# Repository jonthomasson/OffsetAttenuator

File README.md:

# OffsetAttenuator
4MHz Offset Attenuator used in Ham Radio Fox Hunting.

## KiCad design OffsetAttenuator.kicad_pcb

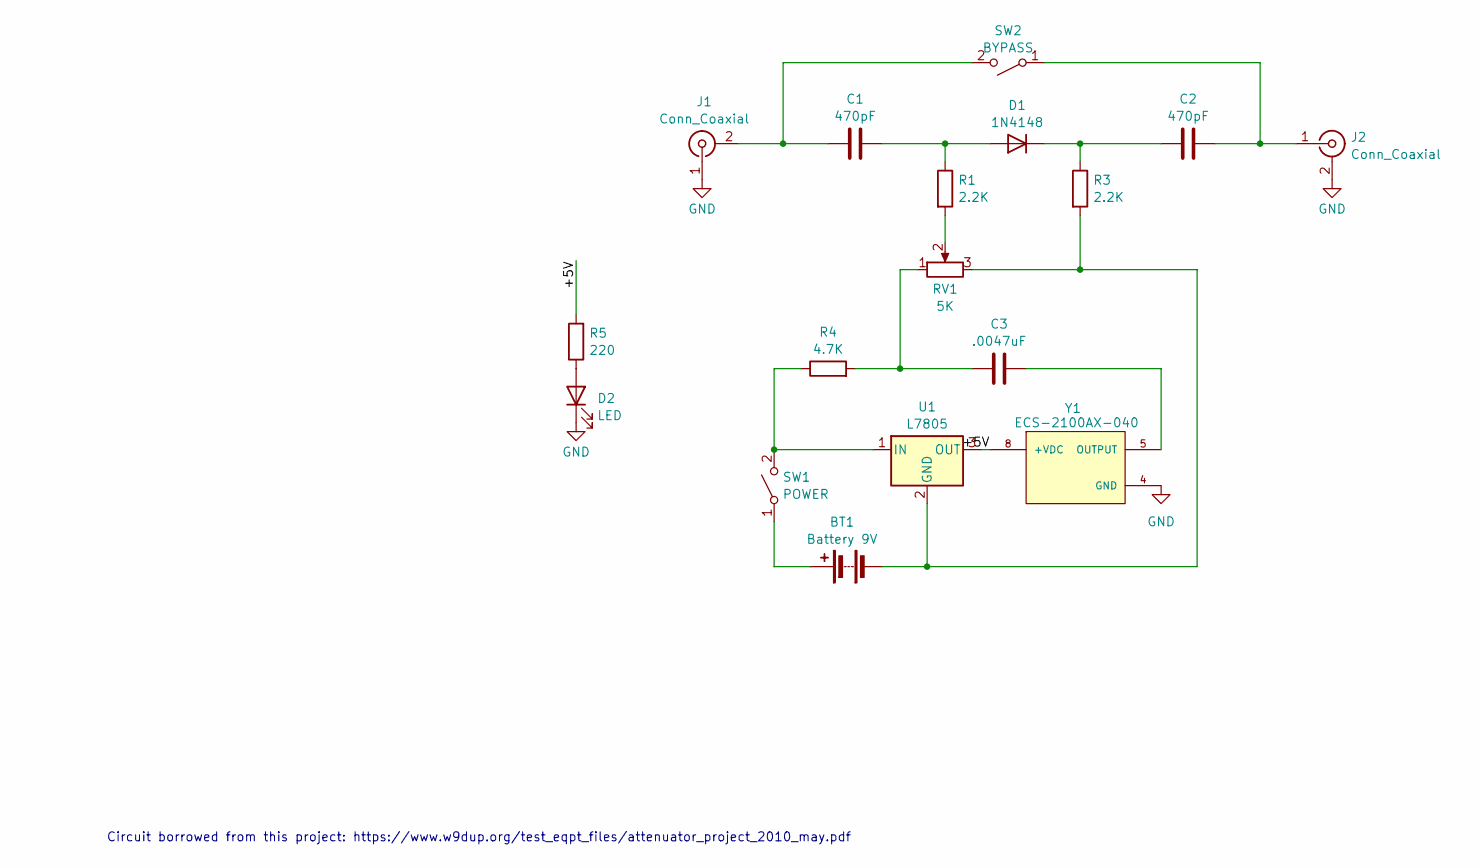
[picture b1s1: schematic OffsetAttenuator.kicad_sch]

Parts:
BT1: Battery 9V; PinHeader_1x02_P2.54mm_Vertical
C1, C2: 470pF; C_Disc_D5.0mm_W2.5mm_P5.00mm
C3: .0047uF; C_Disc_D5.0mm_W2.5mm_P5.00mm
D1: 1N4148; D_DO-35_SOD27_P7.62mm_Horizontal
D2: LED; LED_D5.0mm
J1, J2: Conn_Coaxial; CONBNC002
R1, R3: 2.2K; R_Axial_DIN0309_L9.0mm_D3.2mm_P12.70mm_Horizontal
R4: 4.7K; R_Axial_DIN0309_L9.0mm_D3.2mm_P12.70mm_Horizontal
R5: 220; R_Axial_DIN0309_L9.0mm_D3.2mm_P12.70mm_Horizontal
RV1: 5K; TRIM_3310Y-001-502L
SW1: POWER; SWT3
SW2: BYPASS; SWT3
U1: L7805; TO-220-3_Vertical
Y1: ECS-2100AX-040; OSC_ECS-2100AX-040; PARTREV N/A

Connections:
/+5V: R5.2, U1.3 (OUT), Y1.8 (+VDC)
GND: D2.1 (K), J1.1 (In), J2.2 (Ext), Y1.4 (GND)
unnamed: BT1.1 (+), SW1.1 (A)
unnamed: BT1.2 (-), R3.2, RV1.3, U1.2 (GND)
unnamed: C3.1, R4.2, RV1.1
unnamed: C1.2, D1.2 (A), R1.1
unnamed: C2.1, D1.1 (K), R3.1
unnamed: D2.2 (A), R5.1
unnamed: C1.1, J1.2 (Ext), SW2.2 (B)
unnamed: C2.2, J2.1 (In), SW2.1 (A)
unnamed: R1.2, RV1.2
unnamed: R4.1, SW1.2 (B), U1.1 (IN)
unnamed: C3.2, Y1.5 (OUTPUT)

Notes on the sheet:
Circuit borrowed from this project: https://www.w9dup.org/test_eqpt_files/attenuator_project_2010_may.pdf

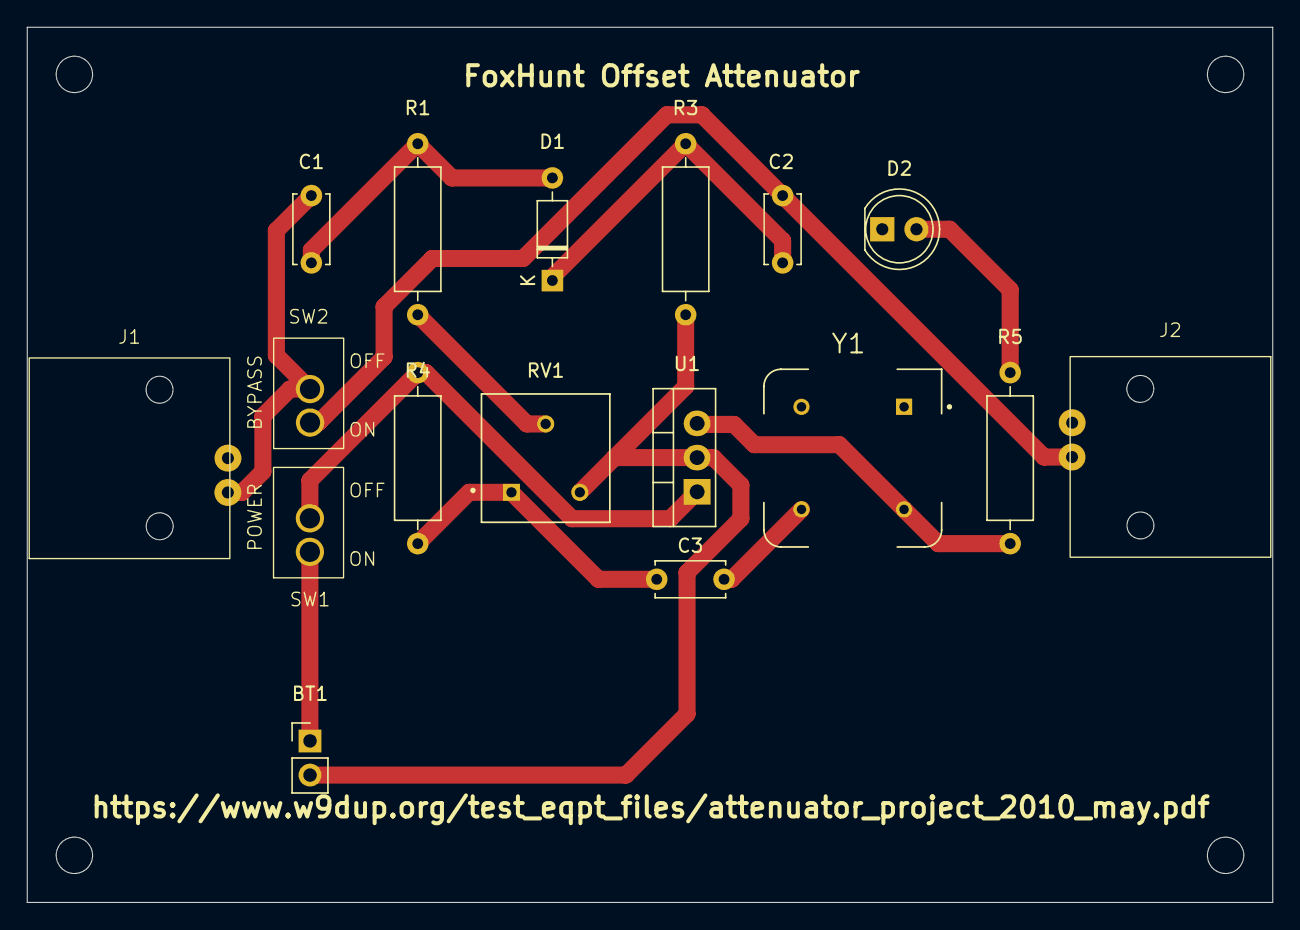
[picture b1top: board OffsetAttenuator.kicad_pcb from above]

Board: 2 copper layers, 92.5 x 65.0 mm, 17 parts (0 on the bottom side), 13 nets.

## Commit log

2024-12-08 updating schematic
2025-01-03 adding bypass toggle
2025-01-07 assigning footprints
2025-03-02 upgrading to kicad 9
2025-03-08 adding footprints and models
2025-03-18 schematic updates
2025-03-21 adding osc schematic and footprint
2025-03-23 begin layout
2025-03-27 pcb layout
2025-04-10 more layout
2025-04-13 begin routing
2025-04-13 adding mounting holes
2025-04-13 updating silkscreen
2025-08-17 adding gerbers
